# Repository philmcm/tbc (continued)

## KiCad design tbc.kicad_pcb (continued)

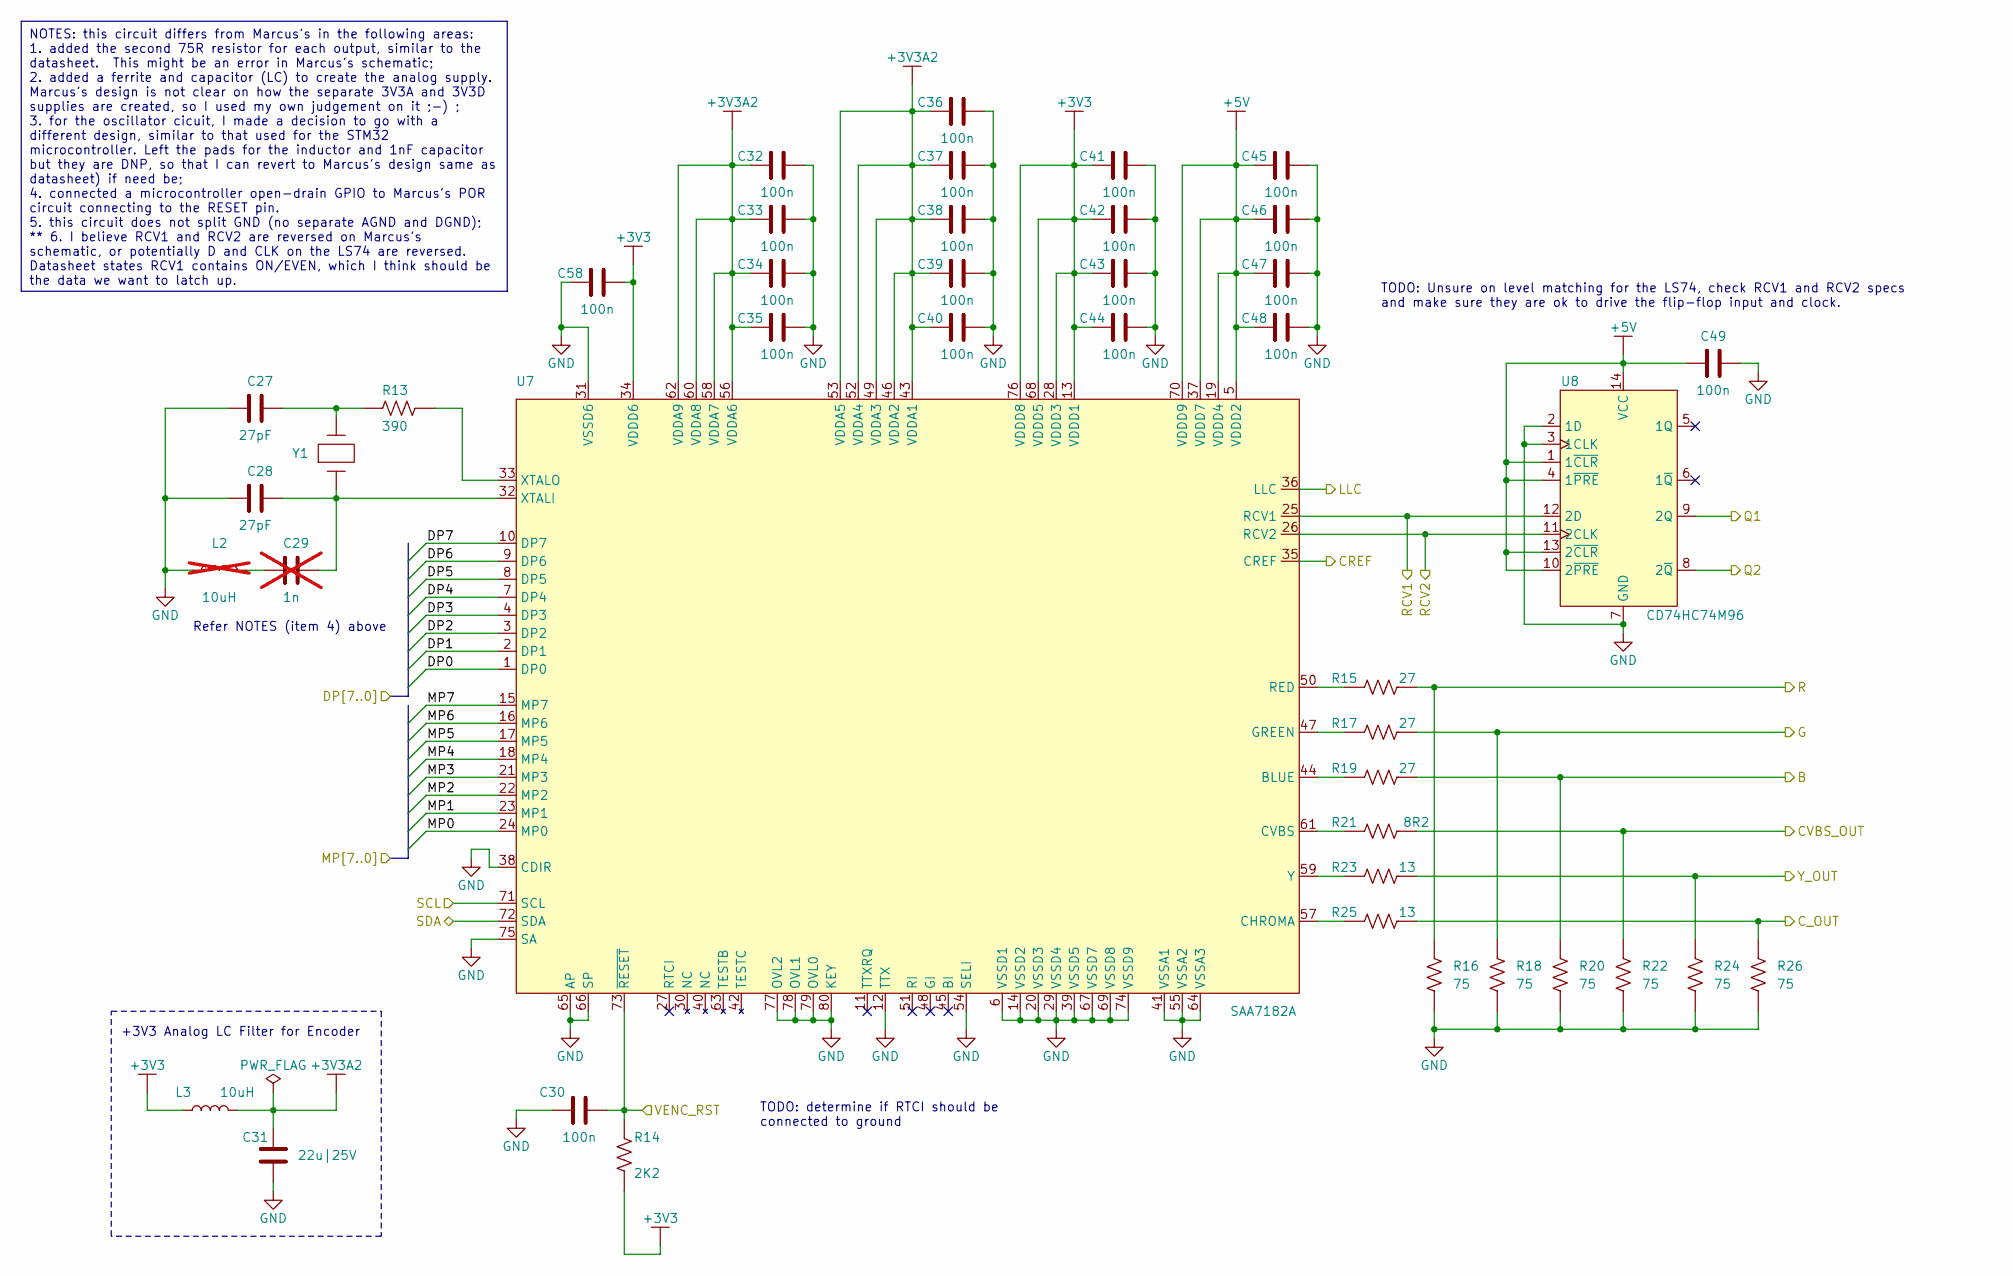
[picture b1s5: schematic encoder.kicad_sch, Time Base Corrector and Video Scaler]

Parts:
C27, C28: 27pF; C0603; Mouser 81-GCM1885C2A270JA6D
C29: 1n; C0603; Mouser 81-GCM1885C2A102FA6D; not fitted
C30, C32, C33, C34, C35, C36, C37, C38, C39, C40, C41, C42, C43, C44, C45, C46, C47, C48, C49, C58: 100n; C0603; Mouser 81-GCJ188R71H104KA2D
C31: 22u|25V; GRM32; Mouser 81-GRM32ER71E226KE5L
L2: 10uH; L0805; Mouser 81-LQM21DH100M70L; not fitted
L3: 10uH; DFE201610E; Mouser 81-DFE201610E-100MP2
R13: 390; R0603; Mouser 603-RC0603FR-07390RL
R14: 2K2; R0603; Mouser 603-RC0603FR-072K2L
R15, R17, R19: 27; R0603; Mouser 603-RC0603FR-0727RL
R16, R18, R20, R22, R24, R26: 75; R0603; Mouser 603-RC0603FR-0775RL
R21: 8R2; R0603; Mouser 603-RC0603FR-078R2L
R23, R25: 13; R0603; Mouser 603-RC0603FR-0713RL
U7: SAA7182A; QFP80_14x20x2.8mm_Pitch0.8mm
U8: CD74HC74M96; SOIC-14; Mouser 595-CD74HC74M96
Y1: ABLS-27.000MHZ-B2F-T; ABLS; Mouser 815-ABLS-27-B2

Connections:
+3V3: C41.1, C42.1, C43.1, C44.1, C58.2, L3.1, R14.1, U7.13 (VDDD1), U7.28 (VDDD3), U7.34 (VDDD6), U7.68 (VDDD5), U7.76 (VDDD8); also elsewhere on the board
+3V3A2: C31.1, C32.1, C33.1, C34.1, C35.1, C36.1, C37.1, C38.1, C39.1, C40.1, L3.2, U7.43 (VDDA1), U7.46 (VDDA2), U7.49 (VDDA3), U7.52 (VDDA4), U7.53 (VDDA5), U7.56 (VDDA6), U7.58 (VDDA7), U7.60 (VDDA8), U7.62 (VDDA9)
+5V: C45.1, C46.1, C47.1, C48.1, C49.1, U7.5 (VDDD2), U7.19 (VDDD4), U7.37 (VDDD7), U7.70 (VDDD9), U8.1 (1~CLR), U8.4 (1~PRE), U8.10 (2~PRE), U8.13 (2~CLR), U8.14 (VCC); also elsewhere on the board
/Frame Memories and Freeze/CREF: U7.35 (CREF); also elsewhere on the board
/Frame Memories and Freeze/DP0: U7.1 (DP0); also elsewhere on the board
/Frame Memories and Freeze/DP1: U7.2 (DP1); also elsewhere on the board
/Frame Memories and Freeze/DP2: U7.3 (DP2); also elsewhere on the board
/Frame Memories and Freeze/DP3: U7.4 (DP3); also elsewhere on the board
/Frame Memories and Freeze/DP4: U7.7 (DP4); also elsewhere on the board
/Frame Memories and Freeze/DP5: U7.8 (DP5); also elsewhere on the board
/Frame Memories and Freeze/DP6: U7.9 (DP6); also elsewhere on the board
/Frame Memories and Freeze/DP7: U7.10 (DP7); also elsewhere on the board
/Frame Memories and Freeze/LLC: U7.36 (LLC); also elsewhere on the board
/Frame Memories and Freeze/MP0: U7.24 (MP0); also elsewhere on the board
/Frame Memories and Freeze/MP1: U7.23 (MP1); also elsewhere on the board
/Frame Memories and Freeze/MP2: U7.22 (MP2); also elsewhere on the board
/Frame Memories and Freeze/MP3: U7.21 (MP3); also elsewhere on the board
/Frame Memories and Freeze/MP4: U7.18 (MP4); also elsewhere on the board
/Frame Memories and Freeze/MP5: U7.17 (MP5); also elsewhere on the board
/Frame Memories and Freeze/MP6: U7.16 (MP6); also elsewhere on the board
/Frame Memories and Freeze/MP7: U7.15 (MP7); also elsewhere on the board
/Frame Memories and Freeze/Q1: U8.9 (2Q); also elsewhere on the board
/Frame Memories and Freeze/Q2: U8.8 (2~Q); also elsewhere on the board
/Frame Memories and Freeze/RCV1: U7.25 (RCV1), U8.12 (2D); also elsewhere on the board
/Frame Memories and Freeze/RCV2: U7.26 (RCV2), U8.11 (2CLK); also elsewhere on the board
/Microcontroller, Power/SCL: U7.71 (SCL); also elsewhere on the board
/Microcontroller, Power/SDA: U7.72 (SDA); also elsewhere on the board
/Microcontroller, Power/VENC_RST: C30.2, R14.2, U7.73 (~RESET); also elsewhere on the board
/Video Encoder/B: R19.2, R20.2; also elsewhere on the board
/Video Encoder/CVBS_OUT: R21.2, R22.2; also elsewhere on the board
/Video Encoder/C_OUT: R25.2, R26.2; also elsewhere on the board
/Video Encoder/G: R17.2, R18.2; also elsewhere on the board
/Video Encoder/R: R15.2, R16.2; also elsewhere on the board
/Video Encoder/Y_OUT: R23.2, R24.2; also elsewhere on the board
GND: C27.2, C28.2, C30.1, C31.2, C32.2, C33.2, C34.2, C35.2, C36.2, C37.2, C38.2, C39.2, C40.2, C41.2, C42.2, C43.2, C44.2, C45.2, C46.2, C47.2, C48.2, C49.2, C58.1, L2.1, R16.1, R18.1, R20.1, R22.1, R24.1, R26.1, U7.6 (VSSD1), U7.12 (TTX), U7.14 (VSSD2), U7.20 (VSSD3), U7.29 (VSSD4), U7.31 (VSSD6), U7.38 (CDIR), U7.39 (VSSD5), U7.41 (VSSA1), U7.54 (SELI), U7.55 (VSSA2), U7.64 (VSSA3), U7.65 (AP), U7.66 (SP), U7.67 (VSSD7), U7.69 (VSSD8), U7.74 (VSSD9), U7.75 (SA), U7.77 (OVL2), U7.78 (OVL1), U7.79 (OVL0), U7.80 (KEY), U8.2 (1D), U8.3 (1CLK), U8.7 (GND); also elsewhere on the board
unnamed: C27.1, R13.2, Y1.2
unnamed: C29.2, L2.2
unnamed: R19.1, U7.44 (BLUE)
unnamed: R25.1, U7.57 (CHROMA)
unnamed: R21.1, U7.61 (CVBS)
unnamed: R17.1, U7.47 (GREEN)
unnamed: R15.1, U7.50 (RED)
unnamed: C28.1, C29.1, U7.32 (XTALI), Y1.1
unnamed: R13.1, U7.33 (XTALO)
unnamed: R23.1, U7.59 (Y)

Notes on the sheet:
NOTES: this circuit differs from Marcus's in the following areas: 1. added the second 75R resistor for each output, similar to the datasheet. This might be an error in Marcus's schematic; 2. added a ferrite and capacitor (LC) to create the analog supply. Marcus's design is not clear on how the sepa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
TODO: Unsure on level matching for the LS74, check RCV1 and RCV2 specs and make sure they are ok to drive the flip-flop input and clock.
+3V3 Analog LC Filter for Encoder
TODO: determine if RTCI should be connected to ground
Refer NOTES (item 4) above

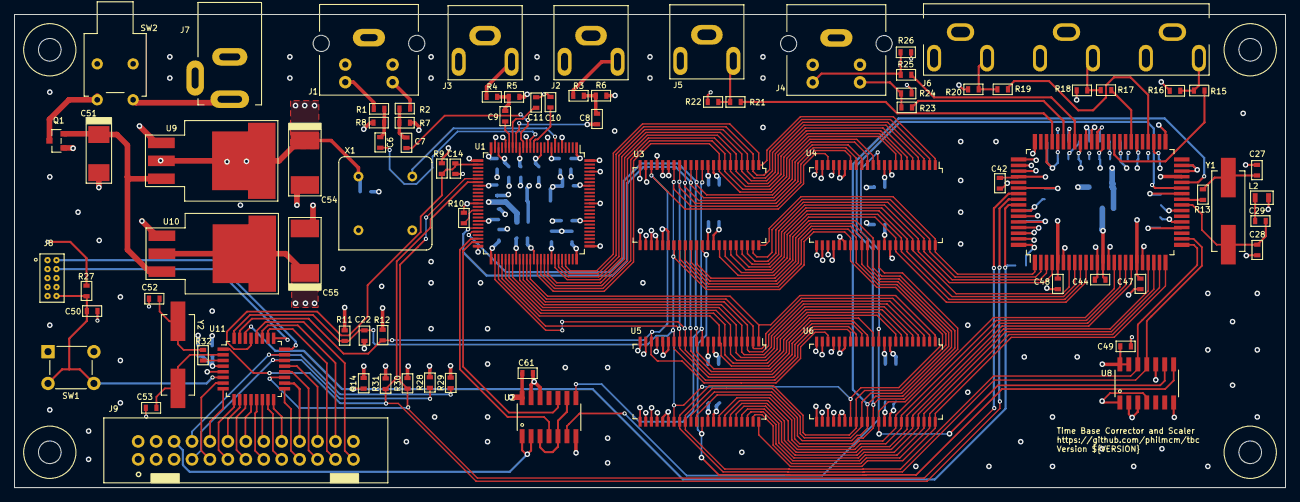
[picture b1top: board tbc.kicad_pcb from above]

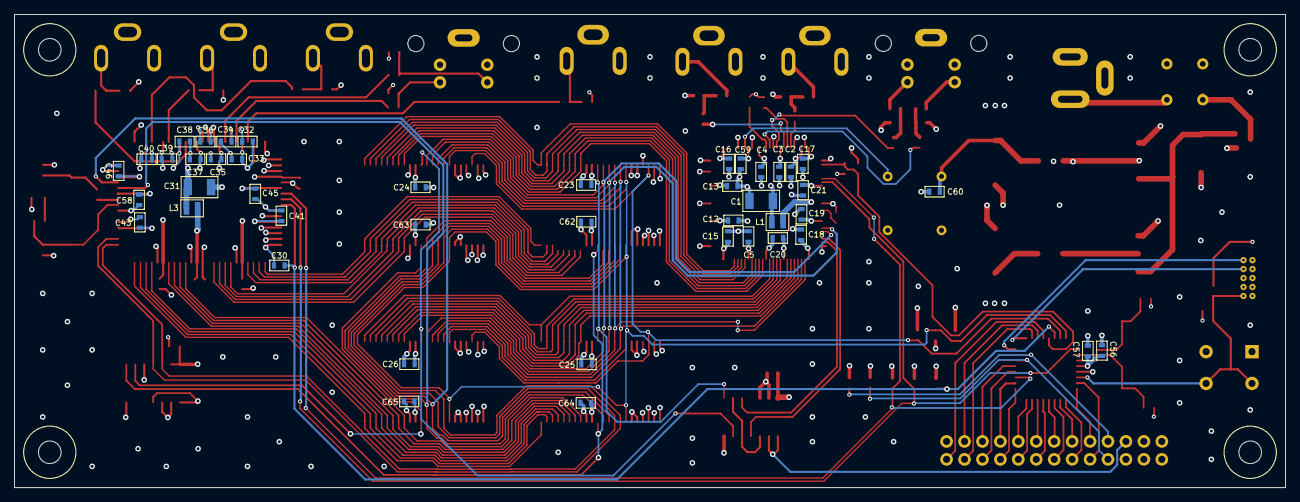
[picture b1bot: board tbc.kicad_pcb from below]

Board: 4 copper layers, 180.0 x 67.0 mm, 130 parts (44 on the bottom side), 119 nets.

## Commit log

2023-04-05 Added .gitignore
2023-11-30 Committed footprints, updated .gitignore
2024-01-15 initial work on schematic symbol creation
2024-01-15 added symbols for i2c res and decoupling cap
2024-01-15 changed hierarchy, added symbols
2024-01-16 continuing schematic capture, renamed sheets
2024-01-16 added decoder symbol
2024-01-16 added buses, title block info
2024-01-16 added frame memory symbol and updated schematic
2024-01-19 continued on schematic, added power sheet
2024-01-22 updates to power, ferrites etc
2024-01-24 added encoder to schematic
2024-01-25 moved UI (2nd board) to its own project, other updates
2024-01-25 renamed micro_ui to micro_power
2024-01-25 major progress with memory interfacing
2024-01-25 minor changes to schematic layout
2024-01-26 added connectors and crystal, osc
2024-01-26 completed and annotated schematic, passed ERC
2024-01-26 connected shunt pins on switchcraft sockets correctly
2024-01-27 added notes, schematic cleanup
2024-01-27 minor cleanup, addition of notes
2024-02-10 added footprints for large ICs
2024-02-10 resistor footprint added
2024-02-11 added connector footprints
2024-02-11 mosfet and tantalum footprints
2024-02-11 completed power footprints
2024-02-12 footprints and 3d models for caps, connectors
2024-02-14 initial work on layout
2024-02-15 converted to 4-layer pcb
2024-02-18 added connector and diode footprint, more layout
2024-02-18 added footprints for crystals and updated layout
2024-02-19 3V3A component footprints + layout work
2024-02-19 layout LHS
2024-02-19 extra bypass cap for memories + more layout
2024-02-20 layout complete and passed DRC
2024-02-22 add PEC11R footprint, minor enhancements to layout
2024-02-22 moved UI footprints to separate library
2024-02-23 update to Kicad 8.0, add gerbers
2024-07-08 added copper pours to layers
2025-01-18 updates from library, performed ERC/DRC, update Kicad 8.0.8
